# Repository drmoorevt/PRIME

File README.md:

A long sordid history of my PhD endeavors. Sorry for the Git worst-practices.
=========

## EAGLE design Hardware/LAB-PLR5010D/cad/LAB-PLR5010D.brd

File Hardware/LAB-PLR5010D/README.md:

LAB-PLR5010D
=========
* This folder contains the technical data for the LAB-PLR5010D (Programmable Linear Regulator (5.0Vmax, 1.0Amax, Dual Configuration). 

cad:  Contains the files and libraries for the schematic and circuit board 
docs: Contains product specification, BOM, datasheets, documentation
revs: Contains board revisions that have gone to manufacture

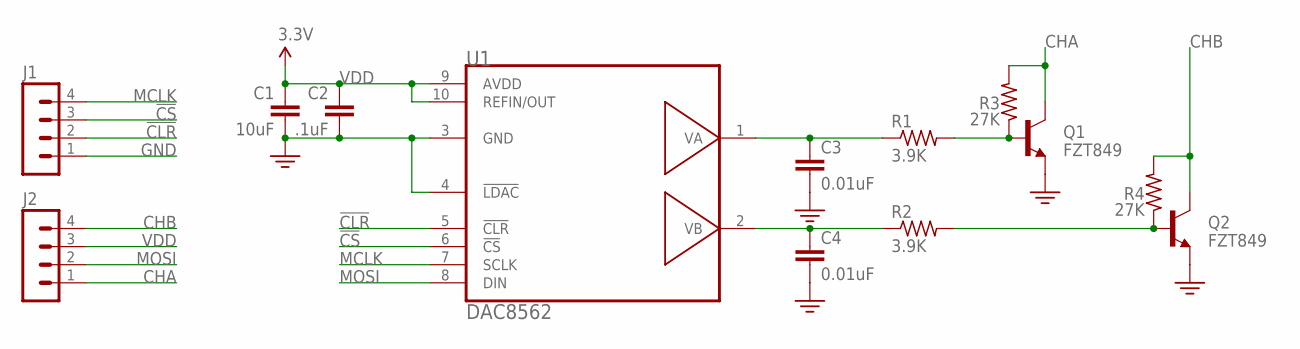
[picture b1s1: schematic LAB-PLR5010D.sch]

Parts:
C1: 10uF; 0603-CAP
C2: .1uF; 0603-CAP
C3, C4: 0.01uF; 0603-CAP
J1, J2: MA04-1
Q1, Q2: FZT849; SOT223
R1, R2: 3.9K; R0603
R3, R4: 27K; R0603
U1: DAC8562; MSOP10

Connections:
!CLR: J1.2, U1.5 (!CLR)
!CS: J1.3, U1.6 (!CS)
CHA: J2.1, Q1.2 (C), Q1.4 (C), R3.2
CHB: J2.4, Q2.2 (C), Q2.4 (C), R4.2
GND: C1.2, C2.2, C3.2, C4.2, J1.1, Q1.3 (E), Q2.3 (E), U1.3 (GND), U1.4 (!LDAC)
MCLK: J1.4, U1.7 (SCLK)
MOSI: J2.2, U1.8 (DIN)
unnamed: C3.1, R1.1, U1.1 (VA)
unnamed: C4.1, R2.1, U1.2 (VB)
unnamed: Q1.1 (B), R1.2, R3.1
unnamed: Q2.1 (B), R2.2, R4.1
VDD: C1.1, C2.1, J2.3, U1.9 (AVDD), U1.10 (REFIN/OUT)

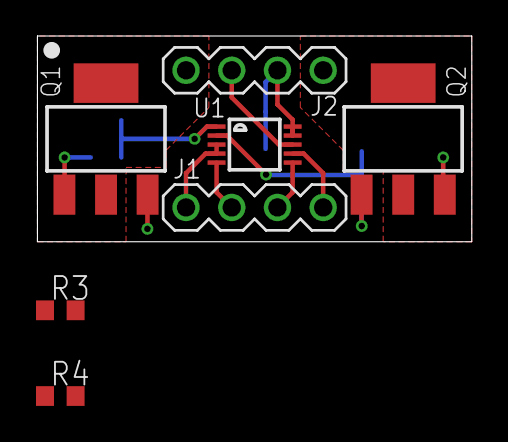
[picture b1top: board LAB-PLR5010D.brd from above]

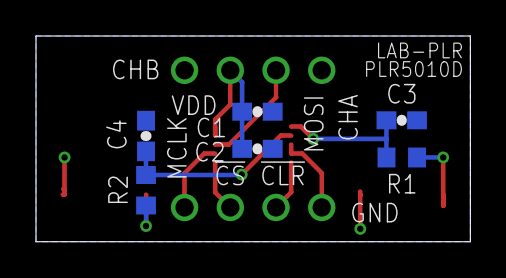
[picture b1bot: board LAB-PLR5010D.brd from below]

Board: 2 copper layers, 24.1 x 11.4 mm, 13 parts (6 on the bottom side), 12 nets.

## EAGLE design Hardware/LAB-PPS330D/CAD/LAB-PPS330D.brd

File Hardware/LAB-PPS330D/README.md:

LAB-PPS330D
=========
* This folder contains the technical data for the LAB-PPS330D (Peripheral Power Switch (3x circuits, 3.0A per circuit) DIP package. 

cad:  Contains the files and libraries for the schematic and circuit board 
docs: Contains product specification, BOM, datasheets, documentation
revs: Contains board revisions that have gone to manufacture

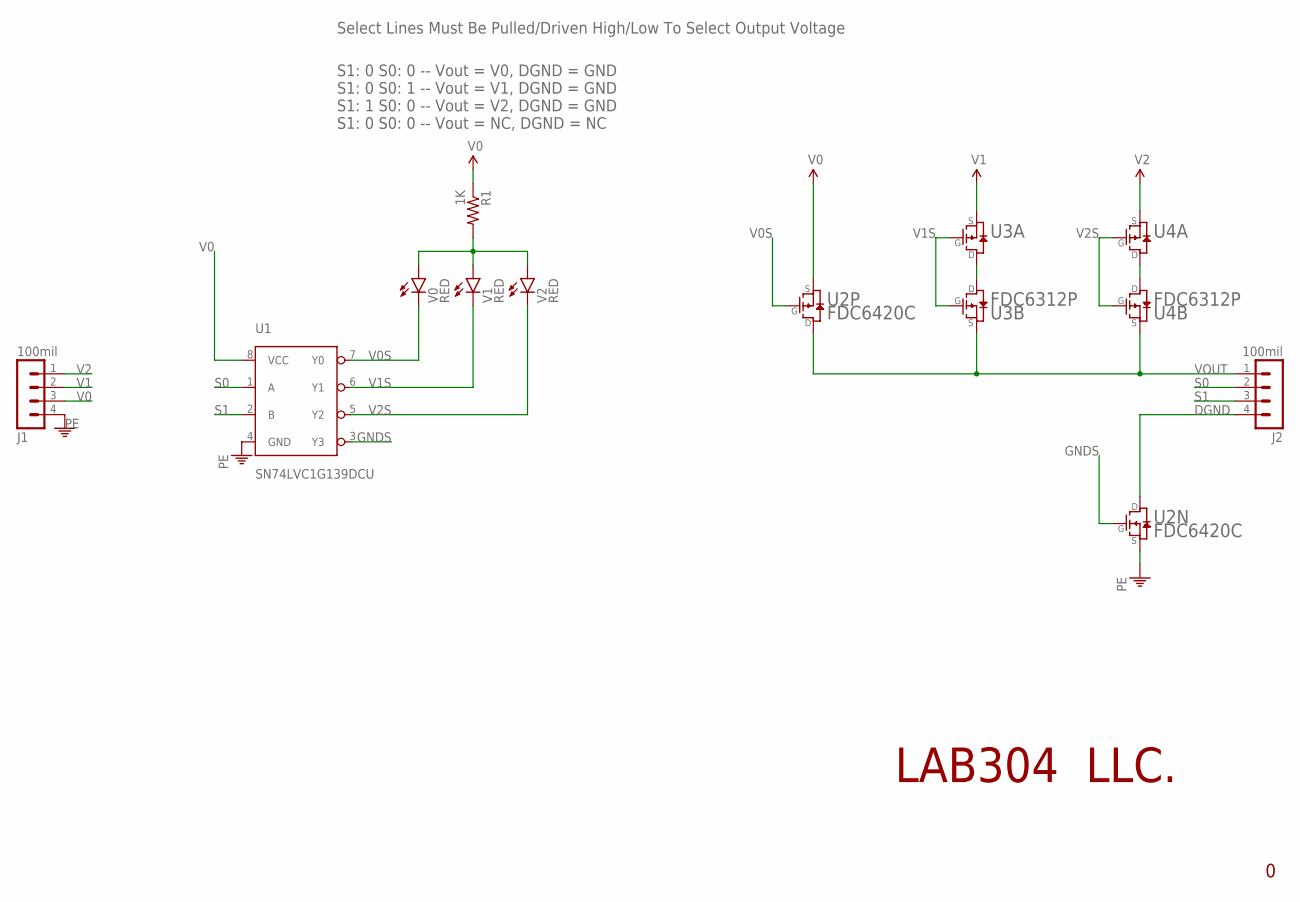
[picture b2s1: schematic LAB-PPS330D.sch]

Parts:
J1, J2: 100mil; MA04-1
R1: 1K; 0603-RES
U1: SN74LVC1G139DCU; SOP50P310X90-8N
U2: FDC6420C; SOT95P270X145-6N
U3, U4: FDC6312P; SOT95P270X145-6N
V0, V1, V2: RED; LED-0603

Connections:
DGND: J2.4, U2.6 (D)
GNDS: U1.3 (Y3), U2.1 (G)
unnamed: U3.4 (D), U3.6 (D)
unnamed: U4.4 (D), U4.6 (D)
unnamed: R1.2, V0.A, V1.A, V2.A
PE: J1.4, U1.4 (GND), U2.5 (S)
S0: J2.2, U1.1 (A)
S1: J2.3, U1.2 (B)
V0: J1.3, R1.1, U1.8 (VCC), U2.2 (S)
V0S: U1.7 (Y0), U2.3 (G), V0.C
V1: J1.2, U3.5 (S)
V1S: U1.6 (Y1), U3.1 (G), U3.3 (G), V1.C
V2: J1.1, U4.5 (S)
V2S: U1.5 (Y2), U4.1 (G), U4.3 (G), V2.C
VOUT: J2.1, U2.4 (D), U3.2 (S), U4.2 (S)

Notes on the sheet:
LAB304 LLC.
Select Lines Must Be Pulled/Driven High/Low To Select Output Voltage
S1: 0 S0: 0 -- Vout = V0, DGND = GND S1: 0 S0: 1 -- Vout = V1, DGND = GND S1: 1 S0: 0 -- Vout = V2, DGND = GND S1: 0 S0: 0 -- Vout = NC, DGND = NC

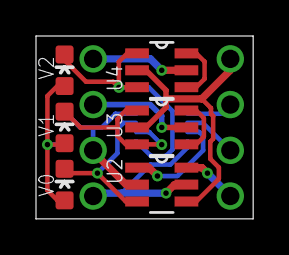
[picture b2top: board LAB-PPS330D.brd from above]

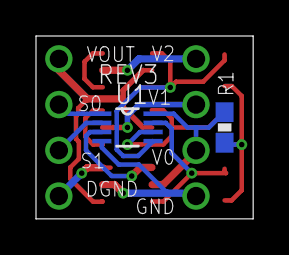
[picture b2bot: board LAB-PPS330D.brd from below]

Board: 2 copper layers, 12.1 x 10.2 mm, 10 parts (2 on the bottom side), 15 nets.

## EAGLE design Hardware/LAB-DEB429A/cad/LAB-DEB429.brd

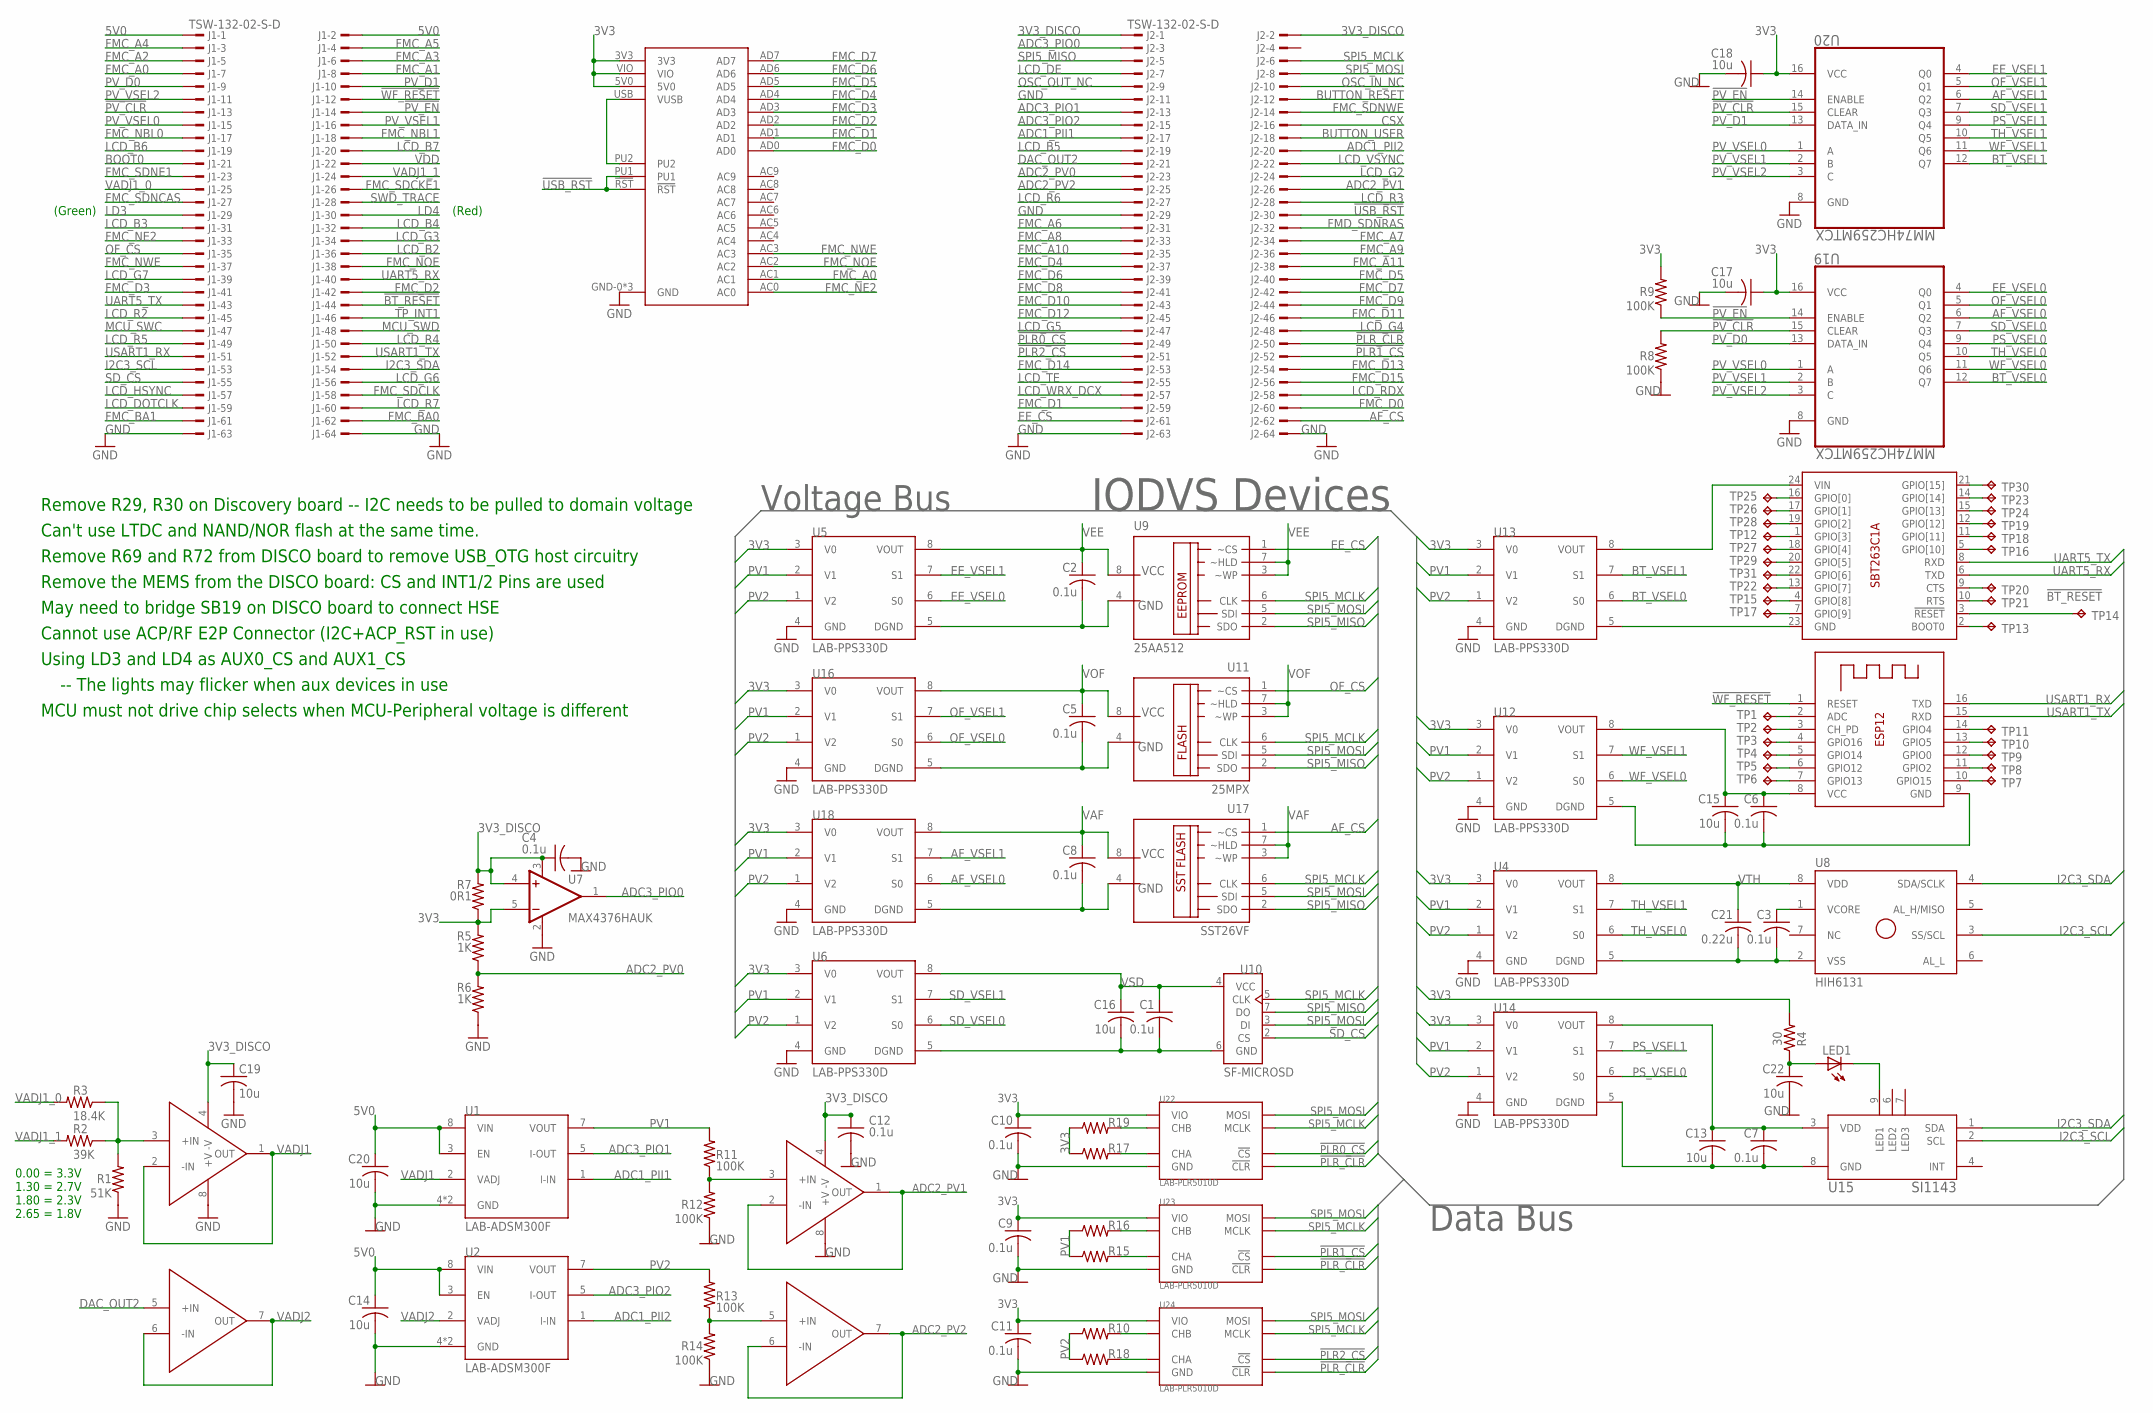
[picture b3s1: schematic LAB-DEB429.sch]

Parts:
C1, C2, C3, C4, C5, C6, C7, C8, C9, C10, C11, C12: 0.1u; C0603
C13, C14, C15, C16, C17, C18, C19, C20, C22: 10u; C0603
C21: 0.22u; C0603
J1, J2: TSW-132-02-S-D
LED1: LEDCHIPLED_1206; CHIPLED_1206
R1: 51K; R0603
R2: 39K; R0603
R3: 18.4K; R0603
R4: 30; R0603
R5, R6: 1K; R0603
R7: 0R1; R0603
R8, R9, R11, R12, R13, R14: 100K; R0603
R10, R15, R16, R17, R18, R19: R-US_0204/7; 0204/7
TP1, TP2, TP3, TP4, TP5, TP6, TP7, TP8, TP9, TP10, TP11, TP12, TP13, TP14, TP15, TP16, TP17, TP18, TP19, TP20, TP21, TP22, TP23, TP24, TP25, TP26, TP27, TP28, TP29, TP30, TP31: TPPAD1-13; P1-13
U1, U2: LAB-ADSM300F; LAB-ASDM300F
U3, U21: LTC6244; MSOP8
U4, U5, U6, U12, U13, U14, U16, U18: LAB-PPS330D
U7: MAX4376HAUK; SOT23-5
U8: HIH6131; SO-08M
U9: 25AA512; SO-08M
U10: SF-MICROSD; MICROSD
U11: 25MPX; SO-08M
U15: SI1143; QFN10
U17: SST26VF; SO-08M
U19, U20: MM74HC259MTCX; SOP65P640X90-16N
U22, U23, U24: LAB-PLR5010D
U25: ESP-12
U26: SPBT2632C1A
U27: UM232H

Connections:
3V3: C9.1, C10.1, C11.1, C17.1, C18.1, R4.2, R5.2, R7.1, R9.2, R17.1, R19.1, U4.3 (V0), U5.3 (V0), U6.3 (V0), U7.5 (-IN), U12.3 (V0), U13.3 (V0), U14.3 (V0), U16.3 (V0), U18.3 (V0), U19.16 (VCC), U20.16 (VCC), U22.VDD (VIO), U23.VDD (VIO), U24.VDD (VIO), U27.3V3, U27.5V0, U27.VIO
3V3_DISCO: C4.1, C12.1, C19.1, J2.1, J2.2, R7.2, U3.4 (-V), U7.3 (V+), U7.4 (+IN), U21.4 (-V)
5V0: C14.1, C20.1, J1.1, J1.2, U1.3 (EN), U1.8 (VIN), U2.3 (EN), U2.8 (VIN)
!BT_RESET: J1.44, TP14.TP, U26.3 (!RESET)
!PLR0_CS: J2.49, U22.!CLR (!CS)
!PLR1_CS: J2.52, U23.!CLR (!CS)
!PLR2_CS: J2.51, U24.!CLR (!CS)
!PLR_CLR: J2.50, U22.!CS (!CLR), U23.!CS (!CLR), U24.!CS (!CLR)
!PV_CLR: J1.13, R8.2, U19.15 (CLEAR), U20.15 (CLEAR)
!PV_EN: J1.14, R9.1, U19.14 (ENABLE), U20.14 (ENABLE)
!USB_RST: J2.30, U27.!RST, U27.PU1
!WF_RESET: J1.12, U25.1 (RESET)
ADC1_PII1: J2.17, U1.1 (I-IN)
ADC1_PII2: J2.20, U2.1 (I-IN)
ADC2_PV0: J2.23, R5.1, R6.2
ADC2_PV1: J2.26, U21.1 (OUT), U21.2 (-IN)
ADC2_PV2: J2.25, U21.6 (-IN), U21.7 (OUT)
ADC3_PIO0: J2.3, U7.1 (OUT)
ADC3_PIO1: J2.13, U1.5 (I-OUT)
ADC3_PIO2: J2.15, U2.5 (I-OUT)
AF_CS: J2.62, U17.1 (~CS)
AF_VSEL0: U18.6 (S0), U19.6 (Q2)
AF_VSEL1: U18.7 (S1), U20.6 (Q2)
BOOT0: J1.21
BT_VSEL0: U13.6 (S0), U19.12 (Q7)
BT_VSEL1: U13.7 (S1), U20.12 (Q7)
BUTTON_RESET: J2.12
BUTTON_USER: J2.18
CSX: J2.16
DAC_OUT2: J2.21, U3.5 (+IN)
EE_CS: J2.61, U9.1 (~CS)
EE_VSEL0: U5.6 (S0), U19.4 (Q0)
EE_VSEL1: U5.7 (S1), U20.4 (Q0)
FMC_A0: J1.7, U27.AC1
FMC_A1: J1.8
FMC_A2: J1.5
FMC_A3: J1.6
FMC_A4: J1.3
FMC_A5: J1.4
FMC_A6: J2.31
FMC_A7: J2.34
FMC_A8: J2.33
FMC_A9: J2.36
FMC_A10: J2.35
FMC_A11: J2.38
FMC_BA0: J1.62
FMC_BA1: J1.61
FMC_D0: J2.60, U27.AD0
FMC_D1: J2.59, U27.AD1
FMC_D2: J1.42, U27.AD2
FMC_D3: J1.41, U27.AD3
FMC_D4: J2.37, U27.AD4
FMC_D5: J2.40, U27.AD5
FMC_D6: J2.39, U27.AD6
FMC_D7: J2.42, U27.AD7
FMC_D8: J2.41
FMC_D9: J2.44
FMC_D10: J2.43
FMC_D11: J2.46
FMC_D12: J2.45
FMC_D13: J2.54
FMC_D14: J2.53
FMC_D15: J2.56
FMC_NBL0: J1.17
FMC_NBL1: J1.18
FMC_NE2: J1.33, U27.AC0
FMC_NOE: J1.38, U27.AC2
FMC_NWE: J1.37, U27.AC3
FMC_SDCKE1: J1.26
FMC_SDCLK: J1.58
FMC_SDNCAS: J1.27
FMC_SDNE1: J1.23
FMC_SDNWE: J2.14
FMD_SDNRAS: J2.32
GND: C1.2, C4.2, C9.2, C10.2, C11.2, C12.2, C14.2, C16.2, C17.2, C18.2, C19.2, C20.2, C22.2, J1.63, J1.64, J2.11, J2.29, J2.63, J2.64, R1.1, R6.1, R8.1, R12.1, R14.1, U1.4 (GND), U1.6 (GND), U2.4 (GND), U2.6 (GND), U3.8 (+V), U4.4 (GND), U5.4 (GND), U6.4 (GND), U6.5 (DGND), U7.2 (V-), U10.6 (GND), U12.4 (GND), U13.4 (GND), U14.4 (GND), U16.4 (GND), U18.4 (GND), U19.8 (GND), U20.8 (GND), U21.8 (+V), U22.CHA (GND), U23.CHA (GND), U24.CHA (GND), U27.GND-0 (GND), U27.GND-1 (GND), U27.SLD (GND)
I2C3_SCL: J1.53, U8.3 (SS/SCL), U15.2 (SCL)
I2C3_SDA: J1.54, U8.4 (SDA/SCLK), U15.1 (SDA)
LCD_B2: J1.36
LCD_B3: J1.31
LCD_B4: J1.32
LCD_B5: J2.19
LCD_B6: J1.19
LCD_B7: J1.20
LCD_DE: J2.7
LCD_DOTCLK: J1.59
LCD_G2: J2.24
LCD_G3: J1.34
LCD_G4: J2.48
LCD_G5: J2.47
LCD_G6: J1.56
LCD_G7: J1.39
LCD_HSYNC: J1.57
LCD_R2: J1.45
LCD_R3: J2.28
LCD_R4: J1.50
LCD_R5: J1.49
LCD_R6: J2.27
LCD_R7: J1.60
LCD_RDX: J2.58
LCD_TE: J2.55
LCD_VSYNC: J2.22
LCD_WRX_DCX: J2.57
LD3: J1.29
LD4: J1.30
MCU_SWC: J1.47
MCU_SWD: J1.48
unnamed: C6.1, C15.1, U12.8 (VOUT), U25.8 (VCC)
unnamed: C2.2, U5.5 (DGND), U9.4 (GND)
unnamed: C22.1, LED1.A, R4.1
unnamed: TP12.TP, U26.1 (GPIO[3])
unnamed: U13.5 (DGND), U26.23 (GND)
unnamed: TP10.TP, U25.13 (GPIO5)
unnamed: TP7.TP, U25.10 (GPIO15)
unnamed: TP13.TP, U26.2 (BOOT0)
unnamed: TP8.TP, U25.11 (GPIO2)
unnamed: TP9.TP, U25.12 (GPIO0)
unnamed: TP11.TP, U25.14 (GPIO4)
unnamed: TP1.TP, U25.2 (ADC)
unnamed: TP2.TP, U25.3 (CH_PD)
unnamed: TP3.TP, U25.4 (GPIO16)
unnamed: TP4.TP, U25.5 (GPIO14)
unnamed: TP5.TP, U25.6 (GPIO12)
unnamed: TP6.TP, U25.7 (GPIO13)
unnamed: TP15.TP, U26.4 (GPIO[8])
unnamed: TP16.TP, U26.5 (GPIO[10])
unnamed: LED1.C, U15.9 (LED1)
unnamed: TP17.TP, U26.7 (GPIO[9])
unnamed: C6.2, C15.2, U12.5 (DGND), U25.9 (GND)
unnamed: TP18.TP, U26.11 (GPIO[11])
unnamed: C5.2, U11.4 (GND), U16.5 (DGND)
unnamed: U27.PU2, U27.USB (VUSB)
unnamed: U13.8 (VOUT), U26.24 (VIN)
unnamed: C3.1, U8.1 (VCORE)
unnamed: TP19.TP, U26.12 (GPIO[12])
unnamed: TP22.TP, U26.13 (GPIO[7])
unnamed: TP23.TP, U26.14 (GPIO[14])
unnamed: C8.2, U17.4 (GND), U18.5 (DGND)
unnamed: TP24.TP, U26.15 (GPIO[13])
unnamed: TP25.TP, U26.16 (GPIO[0])
unnamed: TP26.TP, U26.17 (GPIO[1])
unnamed: TP27.TP, U26.18 (GPIO[4])
unnamed: TP28.TP, U26.19 (GPIO[2])
unnamed: TP29.TP, U26.20 (GPIO[5])
unnamed: C7.2, C13.2, U14.5 (DGND), U15.8 (GND)
unnamed: C3.2, C21.2, U4.5 (DGND), U8.2 (VSS)
unnamed: C7.1, C13.1, U14.8 (VOUT), U15.3 (VDD)
unnamed: TP30.TP, U26.21 (GPIO[15])
unnamed: TP31.TP, U26.22 (GPIO[6])
unnamed: TP20.TP, U26.9 (CTS)
unnamed: TP21.TP, U26.10 (RTS)
unnamed: R17.2, U22.CHB (CHA)
unnamed: R19.2, U22.MCLK (CHB)
unnamed: R16.2, U23.MCLK (CHB)
unnamed: R15.2, U23.CHB (CHA)
unnamed: R10.2, U24.MCLK (CHB)
unnamed: R18.2, U24.CHB (CHA)
unnamed: R13.1, R14.2, U21.5 (+IN)
unnamed: R11.1, R12.2, U21.3 (+IN)
OF_CS: J1.35, U11.1 (~CS)
OF_VSEL0: U16.6 (S0), U19.5 (Q1)
OF_VSEL1: U16.7 (S1), U20.5 (Q1)
OSC_IN_NC: J2.10
OSC_OUT_NC: J2.9
PS_VSEL0: U14.6 (S0), U19.9 (Q4)
PS_VSEL1: U14.7 (S1), U20.9 (Q4)
PV1: R11.2, R15.1, R16.1, U1.7 (VOUT), U4.2 (V1), U5.2 (V1), U6.2 (V1), U12.2 (V1), U13.2 (V1), U14.2 (V1), U16.2 (V1), U18.2 (V1)
PV2: R10.1, R13.2, R18.1, U2.7 (VOUT), U4.1 (V2), U5.1 (V2), U6.1 (V2), U12.1 (V2), U13.1 (V2), U14.1 (V2), U16.1 (V2), U18.1 (V2)
PV_D0: J1.9, U19.13 (DATA_IN)
PV_D1: J1.10, U20.13 (DATA_IN)
PV_VSEL0: J1.15, U19.1 (A), U20.1 (A)
PV_VSEL1: J1.16, U19.2 (B), U20.2 (B)
PV_VSEL2: J1.11, U19.3 (C), U20.3 (C)
SD_CS: J1.55, U10.2 (CS)
SD_VSEL0: U6.6 (S0), U19.7 (Q3)
SD_VSEL1: U6.7 (S1), U20.7 (Q3)
SPI5_MCLK: J2.6, U9.6 (CLK), U10.5 (CLK), U11.6 (CLK), U17.6 (CLK), U22.GND (MCLK), U23.GND (MCLK), U24.GND (MCLK)
SPI5_MISO: J2.5, U9.2 (SDO), U10.7 (DO), U11.2 (SDO), U17.2 (SDO)
SPI5_MOSI: J2.8, U9.5 (SDI), U10.3 (DI), U11.5 (SDI), U17.5 (SDI), U22.MOSI, U23.MOSI, U24.MOSI
SWD_TRACE: J1.28
TH_VSEL0: U4.6 (S0), U19.10 (Q5)
TH_VSEL1: U4.7 (S1), U20.10 (Q5)
TP_INT1: J1.46
UART5_RX: J1.40, U26.6 (TXD)
UART5_TX: J1.43, U26.8 (RXD)
USART1_RX: J1.51, U25.16 (TXD)
USART1_TX: J1.52, U25.15 (RXD)
VADJ1: U1.2 (VADJ), U3.1 (OUT), U3.2 (-IN)
VADJ1_0: J1.25, R3.2
VADJ1_1: J1.24, R2.2
VADJ2: U2.2 (VADJ), U3.6 (-IN), U3.7 (OUT)
VADJIN: R1.2, R2.1, R3.1, U3.3 (+IN)
VAF: C8.1, U17.3 (~WP), U17.7 (~HLD), U17.8 (VCC), U18.8 (VOUT)
VDD: J1.22
VEE: C2.1, U5.8 (VOUT), U9.3 (~WP), U9.7 (~HLD), U9.8 (VCC)
VOF: C5.1, U11.3 (~WP), U11.7 (~HLD), U11.8 (VCC), U16.8 (VOUT)
VSD: C1.1, C16.1, U6.8 (VOUT), U10.4 (VCC)
VTH: C21.1, U4.8 (VOUT), U8.8 (VDD)
WF_VSEL0: U12.6 (S0), U19.11 (Q6)
WF_VSEL1: U12.7 (S1), U20.11 (Q6)

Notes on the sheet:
(Green)
(Red)
Remove R29, R30 on Discovery board -- I2C needs to be pulled to domain voltage
Can't use LTDC and NAND/NOR flash at the same time.
Remove R69 and R72 from DISCO board to remove USB_OTG host circuitry
0.00 = 3.3V 1.30 = 2.7V 1.80 = 2.3V 2.65 = 1.8V
IODVS Devices
Voltage Bus
Data Bus
Remove the MEMS from the DISCO board: CS and INT1/2 Pins are used
May need to bridge SB19 on DISCO board to connect HSE
Cannot use ACP/RF E2P Connector (I2C+ACP_RST in use)
Using LD3 and LD4 as AUX0_CS and AUX1_CS
-- The lights may flicker when aux devices in use
MCU must not drive chip selects when MCU-Peripheral voltage is different

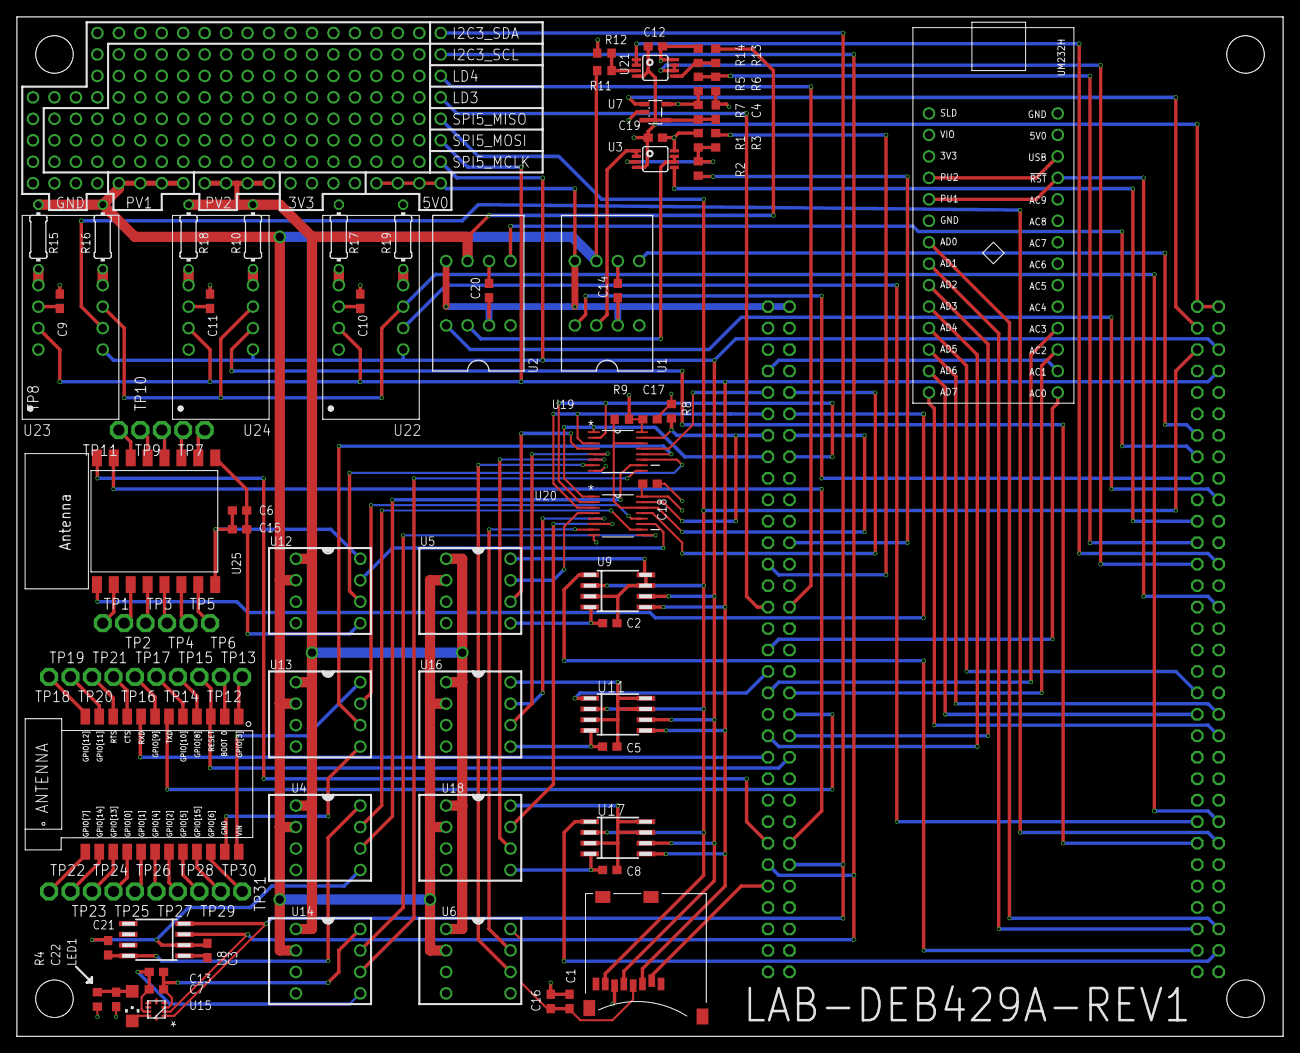
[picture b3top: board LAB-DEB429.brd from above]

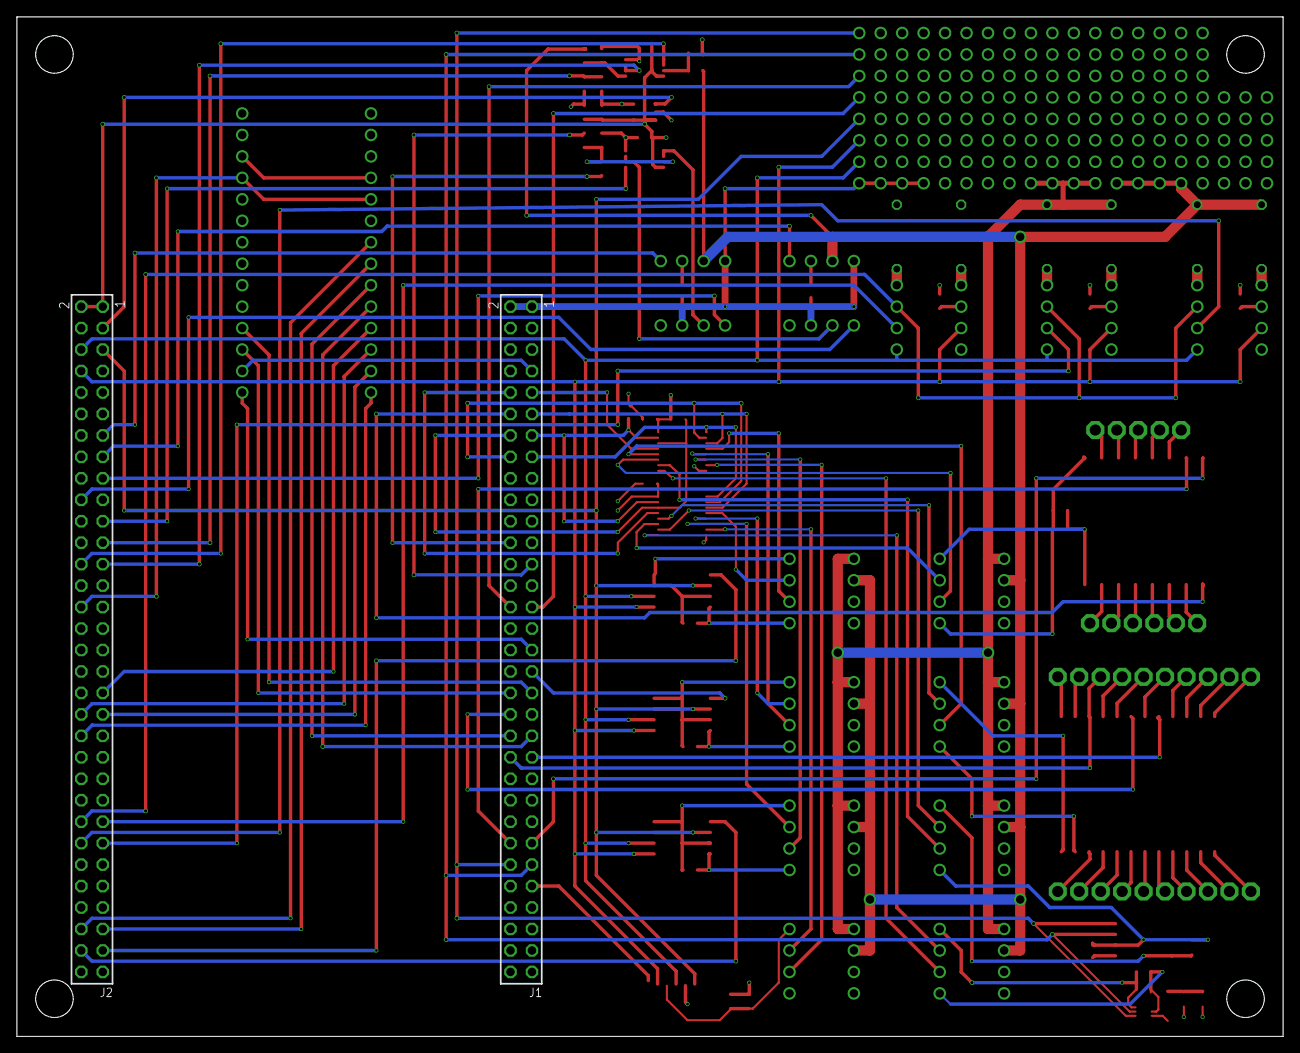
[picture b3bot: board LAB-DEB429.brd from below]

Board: 4 copper layers, 149.9 x 120.7 mm, 102 parts (2 on the bottom side), 132 nets.

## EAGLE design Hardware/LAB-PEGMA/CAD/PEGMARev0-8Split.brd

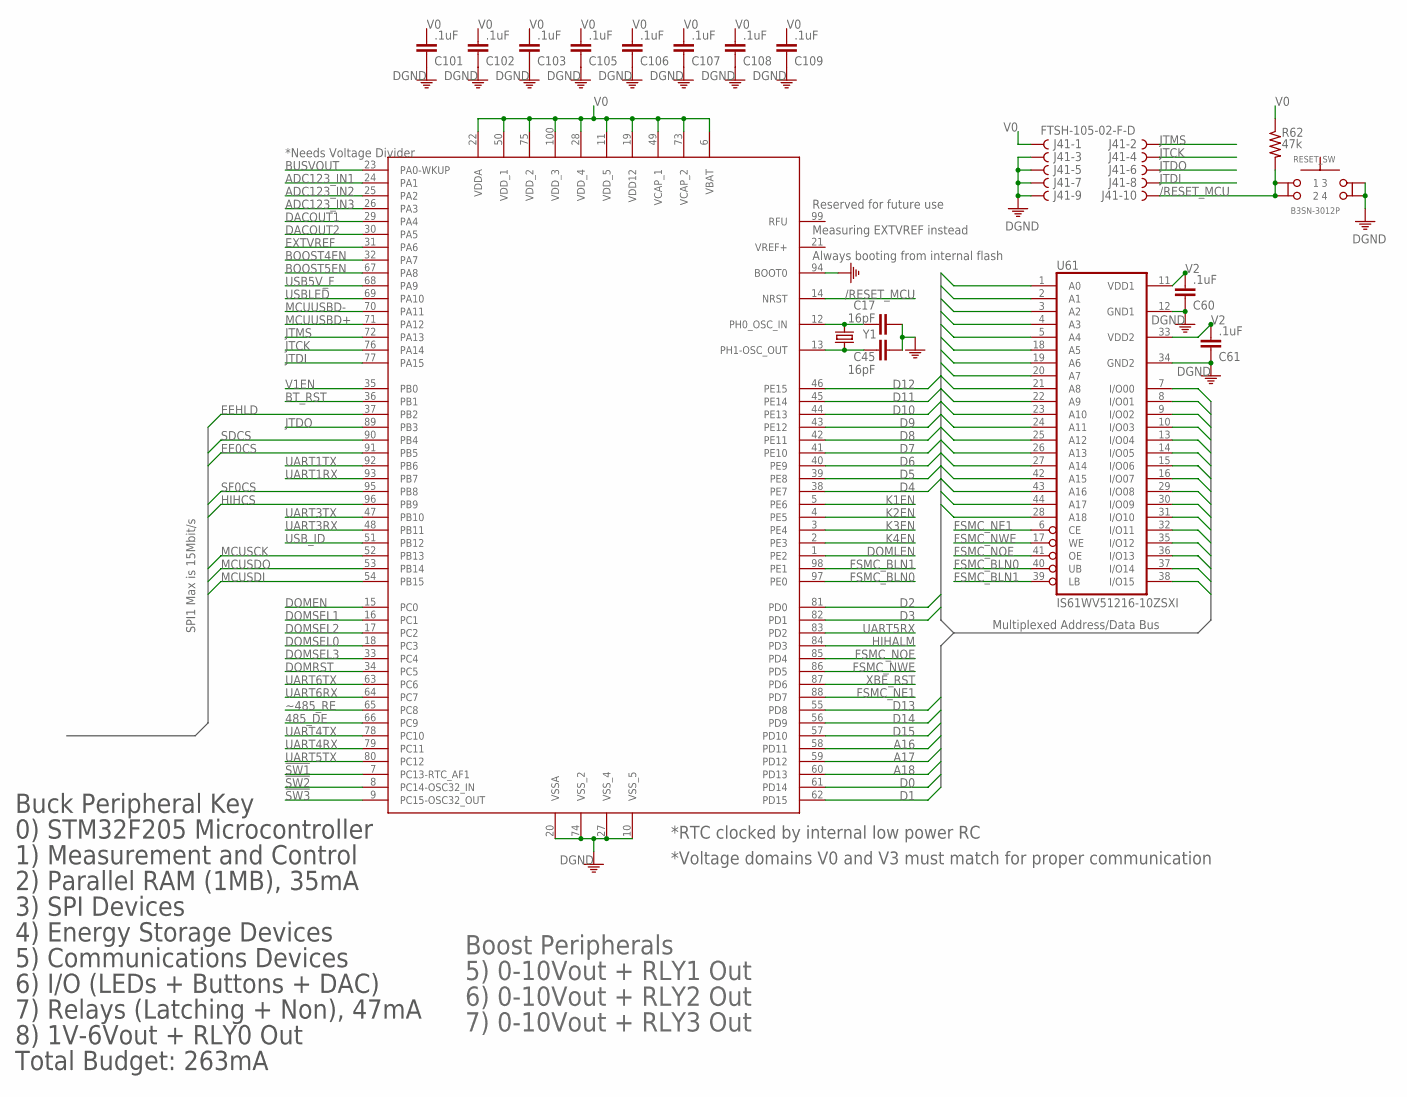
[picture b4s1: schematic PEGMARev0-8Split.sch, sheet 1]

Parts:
C17, C45: 16pF; C0603
C60, C61, C101, C102, C103, C105, C106, C107, C108, C109: .1uF; C0603
J41: FTSH-105-02-F-D; 1296-10
R62: 47k; R0603
RESET_SW: B3SN-3012P; SWITCH(B3SN)
U1: STM32F205VG; PZ100
U61: IS61WV51216-10ZSXI; TSOPII-Z44
Y1: CRYSTALHC49UP; HC49UP

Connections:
485_DE: U1.66 (PC9); also elsewhere on the board
!SW1: U1.7 (PC13-RTC_AF1); also elsewhere on the board
!SW2: U1.8 (PC14-OSC32_IN); also elsewhere on the board
!SW3: U1.9 (PC15-OSC32_OUT); also elsewhere on the board
/RESET_MCU: J41.10, R62.2, RESET_SW.1, RESET_SW.2, U1.14 (NRST)
A16: U1.58 (PD11), U61.43 (A16)
A17: U1.59 (PD12), U61.44 (A17)
A18: U1.60 (PD13), U61.28 (A18)
ADC123_IN1: U1.24 (PA1); also elsewhere on the board
ADC123_IN2: U1.25 (PA2); also elsewhere on the board
ADC123_IN3: U1.26 (PA3); also elsewhere on the board
BOOST4EN: U1.32 (PA7); also elsewhere on the board
BOOST5EN: U1.67 (PA8); also elsewhere on the board
BT_RST: U1.36 (PB1); also elsewhere on the board
BUSVOUT: U1.23 (PA0-WKUP); also elsewhere on the board
D0: U1.61 (PD14), U61.1 (A0), U61.7 (I/O00)
D1: U1.62 (PD15), U61.2 (A1), U61.8 (I/O01)
D2: U1.81 (PD0), U61.3 (A2), U61.9 (I/O02)
D3: U1.82 (PD1), U61.4 (A3), U61.10 (I/O03)
D4: U1.38 (PE7), U61.5 (A4), U61.13 (I/O04)
D5: U1.39 (PE8), U61.14 (I/O05), U61.18 (A5)
D6: U1.40 (PE9), U61.15 (I/O06), U61.19 (A6)
D7: U1.41 (PE10), U61.16 (I/O07), U61.20 (A7)
D8: U1.42 (PE11), U61.21 (A8), U61.29 (I/O08)
D9: U1.43 (PE12), U61.22 (A9), U61.30 (I/O09)
D10: U1.44 (PE13), U61.23 (A10), U61.31 (I/O10)
D11: U1.45 (PE14), U61.24 (A11), U61.32 (I/O11)
D12: U1.46 (PE15), U61.25 (A12), U61.35 (I/O12)
D13: U1.55 (PD8), U61.26 (A13), U61.36 (I/O13)
D14: U1.56 (PD9), U61.27 (A14), U61.37 (I/O14)
D15: U1.57 (PD10), U61.38 (I/O15), U61.42 (A15)
DACOUT1: U1.29 (PA4); also elsewhere on the board
DACOUT2: U1.30 (PA5); also elsewhere on the board
DOMEN: U1.15 (PC0); also elsewhere on the board
DOMLEN: U1.1 (PE2); also elsewhere on the board
DOMRST: U1.34 (PC5); also elsewhere on the board
DOMSEL0: U1.18 (PC3); also elsewhere on the board
DOMSEL1: U1.16 (PC1); also elsewhere on the board
DOMSEL2: U1.17 (PC2); also elsewhere on the board
DOMSEL3: U1.33 (PC4); also elsewhere on the board
EE0CS: U1.91 (PB5); also elsewhere on the board
EEHLD: U1.37 (PB2); also elsewhere on the board
EXTVREF: U1.31 (PA6); also elsewhere on the board
FSMC_BLN0: U1.97 (PE0), U61.40 (UB)
FSMC_BLN1: U1.98 (PE1), U61.39 (LB)
FSMC_NE1: U1.88 (PD7), U61.6 (CE)
FSMC_NOE: U1.85 (PD4), U61.41 (OE)
FSMC_NWE: U1.86 (PD5), U61.17 (WE)
HIHALM: U1.84 (PD3); also elsewhere on the board
HIHCS: U1.96 (PB9); also elsewhere on the board
JTCK: J41.4, U1.76 (PA14)
JTDI: J41.8, U1.77 (PA15)
JTDO: J41.6, U1.89 (PB3)
JTMS: J41.2, U1.72 (PA13)
K1EN: U1.5 (PE6); also elsewhere on the board
K2EN: U1.4 (PE5); also elsewhere on the board
K3EN: U1.3 (PE4); also elsewhere on the board
K4EN: U1.2 (PE3); also elsewhere on the board
MCUSCK: U1.52 (PB13); also elsewhere on the board
MCUSDI: U1.54 (PB15); also elsewhere on the board
MCUSDO: U1.53 (PB14); also elsewhere on the board
MCUUSBD+: U1.71 (PA12); also elsewhere on the board
MCUUSBD-: U1.70 (PA11); also elsewhere on the board
unnamed: C17.2, U1.12 (PH0_OSC_IN), Y1.2
unnamed: C45.1, U1.13 (PH1-OSC_OUT), Y1.1
PE: C17.1, C45.2, C60.1, C61.1, C101.1, C102.1, C103.1, C105.1, C106.1, C107.1, C108.1, C109.1, J41.3, J41.5, J41.7, J41.9, RESET_SW.3, RESET_SW.4, U1.10 (VSS_5), U1.20 (VSSA), U1.27 (VSS_4), U1.74 (VSS_2), U1.94 (BOOT0), U61.12 (GND1), U61.34 (GND2); also elsewhere on the board
SDCS: U1.90 (PB4); also elsewhere on the board
SF0CS: U1.95 (PB8); also elsewhere on the board
UART1RX: U1.93 (PB7); also elsewhere on the board
UART1TX: U1.92 (PB6); also elsewhere on the board
UART3RX: U1.48 (PB11); also elsewhere on the board
UART3TX: U1.47 (PB10); also elsewhere on the board
UART4RX: U1.79 (PC11); also elsewhere on the board
UART4TX: U1.78 (PC10); also elsewhere on the board
UART5RX: U1.83 (PD2); also elsewhere on the board
UART5TX: U1.80 (PC12); also elsewhere on the board
UART6RX: U1.64 (PC7); also elsewhere on the board
UART6TX: U1.63 (PC6); also elsewhere on the board
USB5V_F: U1.68 (PA9); also elsewhere on the board
USBLED: U1.69 (PA10); also elsewhere on the board
USB_ID: U1.51 (PB12); also elsewhere on the board
V0: C101.2, C102.2, C103.2, C105.2, C106.2, C107.2, C108.2, C109.2, J41.1, R62.1, U1.6 (VBAT), U1.11 (VDD_5), U1.19 (VDD12), U1.22 (VDDA), U1.28 (VDD_4), U1.49 (VCAP_1), U1.50 (VDD_1), U1.73 (VCAP_2), U1.75 (VDD_2), U1.100 (VDD_3); also elsewhere on the board
V1EN: U1.35 (PB0); also elsewhere on the board
V2: C60.2, C61.2, U61.11 (VDD1), U61.33 (VDD2); also elsewhere on the board
XBE_RST: U1.87 (PD6); also elsewhere on the board
~485_RE: U1.65 (PC8); also elsewhere on the board

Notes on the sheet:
Buck Peripheral Key
1) Measurement and Control
2) Parallel RAM (1MB), 35mA
3) SPI Devices
4) Energy Storage Devices
5) Communications Devices
6) I/O (LEDs + Buttons + DAC)
7) Relays (Latching + Non), 47mA
8) 1V-6Vout + RLY0 Out
0) STM32F205 Microcontroller
Total Budget: 263mA
Multiplexed Address/Data Bus
*RTC clocked by internal low power RC
Boost Peripherals
5) 0-10Vout + RLY1 Out
6) 0-10Vout + RLY2 Out
7) 0-10Vout + RLY3 Out
*Voltage domains V0 and V3 must match for proper communication
Reserved for future use
Measuring EXTVREF instead
Always booting from internal flash
SPI1 Max is 15Mbit/s
*Needs Voltage Divider

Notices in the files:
parts and their libraries:
SparkFun-AnalogIC: Licensing:Creative Commons ShareAlike 4.0 International - https://creativecommons.org/licenses/by-sa/4.0
